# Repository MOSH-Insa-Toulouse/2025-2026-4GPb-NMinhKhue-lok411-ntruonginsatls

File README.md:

# Projet: Capteur Graphite à Crayon
MOSH projet crée par les étudiant.es en 4ème année de Génie Physique: 
**NGUYEN Minh Khue, VO Phuc Loc, TRUONG Nguyen Gia Khanh**

# Tableau de matière
- [Introduction](#introduction)
  - [Objectifs](#1-objectifs)
  - [Conception](#2-conception)
  - [Matériels nécessaires](#3-matériels-nécessaires)
  - [Livrables](#4-livrables)
- [Réalisation du projet](#réalisation-du-projet)
  - [Schémas](#1-schémas)
    - [Wiring diagram et Simulation LTspice](#11-wiring-diagram-et-simulation-ltspice)
    - [Connection diagram et KiCad](#12-connection-diagram-et-kicad)
  - [Software](#2-software)
    - [Code Arduino](#21-code-arduino)
    - [Application Android sur MIT App Inventor](#22-application-android-sur-mit-app-inventor)
  - [Banc de test](#3-banc-de-test)
    - [Principe](#31-principe)
    - [Résultats](#32-résultats)
- [Conclusion](#conclusion)
- [Contacts](#contacts)
## Introduction

### 1. Objectifs
Le projet est dans le cadre de l’UF « Du capteur au banc de test en open source hardware » en 4ᵉ année de Génie Physique à l’INSA Toulouse. Il est inspiré du rapport scientifique "Pencil Drawn Strain Gauges and Chemiresistors on Paper", publié en 2014 par Cheng-Wei Lin*, Zhibo Zhao*, Jaemyung Kim & Jiaxing Huang dans lequel les auteurs ont proposé un nouveau type de jauge de contrainte basé sur graphite. Le principe repose sur le fait que la résistance électrique du graphite varie lorsque le papier est déformé. En effet, la déformation modifie la distance entre les grains de graphite, ce qui entraîne une variation de la conductance du capteur. En mesurant cette variation de résistance, il est possible d’estimer la contrainte appliquée.

Le premier objectif est donc de concevoir un système qui nous permet de faire un banc de test en mesurant les capteurs simples à graphite pour les comparer avec les capteurs commerciales. De plus, le système doit être contrôlable. Le deuximème objectif est d'évaluer l'industriabilité de ce nouveau type de capteur à partir des mesures.

### 2. Conception
Pour regrouper plusieurs fonctions, cela vaut mieux que nous réalisons un shield Arduino. Nous pouvons contrôler les mesures soit manuellement avec un encoder rotatif via un écran OLED, soit à distance via un module Bluetooth et une application Android. Toutes ces idées sont synthétisé dans la figure ci-dessous.

Les détails sont décrits dans la partie de la réalisation.

(apres) nous avons manuellement soudé l'ensemble des modules arduino et composants électroniques (résistances, capacités, amplificateur opérationnel) au PCB imprimé.

(apres) Le Shield réalisé intègre un amplificateur de signal LTC1050 pour amplifier les faibles signaux des capteurs avec précision, un encodeur rotatif permettant de naviguer dans le menu et de modifier les valeurs de résistance via un potentiomètre, un écran OLED pour afficher clairement les menus et les informations, ainsi qu’un module Bluetooth assurant la communication sans fil avec un téléphone portable pour le contrôle et la supervision à distance du système.

### 3. Matériels nécessaires 
Avec la conception, nous avons décidé que ces composants listés ci-dessous sont suffisants, tout est disponible dans la salle d'instrumentation :
- 1 Carte Arduino UNO
- 1 Module Bluetooth (HC-05)
- 1 Encoder rotatif (Keyes KY-040)
- 1 Écran OLED
- 1 Capteur en graphite fait à l'aide de la couche d'un crayon de papier
- 1 Capteur de flexion commercial (LLC 1070)
- 1 Potentiomètre numérique (MCP41100)
- 1 Amplificateur de transimpédance (LTC1050)
- 2 Supports IC 
- 1 Résistance 1kΩ, 2 résistances 10kΩ, 2 résistances 100kΩ
- 3 condensateurs 100nF, 1 condensateur 1µF

### 4. Livrables
Plusieurs livrables sont contenus dans notre repositoire :
- **Un shield PCB connecté à une carte Arduino UNO** avec differents composants.
- Fiches techniques des composants (HC-05, Keyes KY-040, SSD 1306, LLC 1070, LTC1050, MCP41100)
- **Un code Arduino** qui gère les différents composants cités précédemments (mesures de résistance d'une jauge de contrainte faite en graphite, la communication avec un module Bluetooth, l'affichage sur l'écran OLED d'actions possibles et la gestion du potentiomètre digital permettant la calibration de notre capteur).
- **Une application Android** (grâce aux Tutoriels MIT App Inventor) permet de connecter le PCB et le code Arduino.
- La datasheet du capteur de contrainte en graphite.
- Les fichiers de simulation LTSpice et KiCad.

## Réalisation du projet

### 1. Schémas
La réalisation doit tout d'abord commencer par des schémas électriques tels que le Wiring diagram et le Connection diagram.

#### 1.1. Wiring diagram et Simulation LTspice
Ce diagramme a pour but de savoir comment on peut connecter le capteur à l'Arduino afin que les signaux des mesures soient captées par l'Arduino.

Nous souhaitons mesurer la résistance de notre capteur en graphite. Lorsque la résistance interne de notre capteur de graphite est de l'ordre du GΩ. Le courant généré lorsque nous appliquons une tension de 5V est très faible. Pour pouvoir utiliser ce signal, nous le faisons passer par un amplificateur transimpédance (ici nous choisissons LTC 1050) car il possède une capacité à accepter en entrée un courant très faible et un offset de tension bas. Ce montage est constitué d'un amplificateur opérationnel (AO) pour fournir un signal suffisamment large au convertisseur analogique-numérique (ADC) de l'Arduino UNO.

En plus de l'AOP, nous ajoutons 3 filtres:
- À l'entrée, un filtre passe bas passif composé de R1 et C1 de fréquence de coupure de 16Hz pour filtrer les bruits en courant sur le signal d'entrée.
- Une filtre passe bas actif composé de R3 et C4 de fréquence de coupure de 1.6Hz permettane de filtre la composante de bruit à 50Hz provenant du couplage avec le réseau éléctrique.
- En sortie, un dernier filtre composé de R6 et C2 de fréquence de 1.6kHz qui permet de retirer le bruit créé pendant le traitement i.e. bruits des alimentations, de l'horloge, etc.

La résistance R5 est placé en amont de l'AO pour le protéger contre des décharges électrostatiques. Pour notre simulation, nous avons placé la capacité C3 de sorte à ce qu'elle filtre le bruit de l'alimentation. Ainsi, la résistance R2 sera remplacé par une résistance variable (un potentiomètre digital) qui va nous permettre de régler le gain de notre AO en fonction de notre besoin.

Une fois dessiné le Wiring diagram, nous avons vérifié ses comportements et les valeurs de ses composants électriques (résistances, condensateurs,e tc.) grâce aux simulations du logiciel LTspice. (voir l'onglet caché ci-dessous)
<details>
<summary><strong>Simulation LTspice</strong></summary>

- **Fonctionnalité de condition nominale**

Le courant d’entrée Isens varie entre 50 nA et 100 nA, ce qui entraîne une variation de la tension Vep appliquée à l’entrée non-inverseur V+ du LTC1050, entre 5 mV et 10 mV.

Le gain de l’amplificateur du LTC1050 est défini par : G = 1 + R3/R2 = 101. Par conséquent, la valeur de la tension de sortie du LTC1050 varie entre 0.5 V et 1 V.

Au départ, le signal exprimé en décibels est de 140 dB, ce qui correspond à : 20 log(VADC / Isens).

Le microcontrôleur utilisé est un Arduino UNO, basé sur un microcontrôleur AVR avec une fréquence d’échantillonnage maximale fech = 200 kHz.
Comme la conversion analogique-numérique se fait sur 13 bits, la fréquence d’échantillonnage réelle est limitée à 15.4 kHz.

D'après le théorème de Nyquist, la fréquence maximale du signal que l'on peut correctement numériser doit donc être inférieure à la moitié de cette valeur :
fsignal < fech/2 = 7.7 kHz.

- **Modélisation du capteur**
  - Le bruit à 50 Hz, généré notamment par l'écran TFT (bruit de type secteur), est clairement observé dans le spectre du signal. Pour l’atténuer, on agit sur le condensateur C4 du filtre passe-bas.

  - Lorsque la valeur de C4 est augmentée à 10 µF, le pic de bruit à 50 Hz est fortement réduit, ce qui indique une amélioration de l’atténuation dans les basses fréquences.

  - En revanche, si on diminue la valeur de C4, le bruit augmente, montrant que la fréquence de coupure du filtre remonte et que le bruit secteur passe plus facilement.

- **Résultat**
Une photo démontrant que notre circuit permet une amplification efficace du signal délivré par le capteur :

</details>

#### 1.2. Connection diagram et KiCad
Après le Wiring diagram, nous avons dessiné le diagramme des connexions afin de déterminer les connexions entre les broches des différents composants. Nous l'avons réalisé avec le logiciel KiCad car ce logiciel nous aiderait les étapes après.

Nous vous expliquons les réalisations sur KiCad :

- Réalisation des symboles et des empreints :
Pour commencer notre PCB (Printed Circuit Board), il est nécessaire de créer les symboles et les empreintes des composants qui ne sont pas disponibles dans la bibliothèque de KiCad. Nous avons réalisé les symboles du module Bluetooth, de l'encodeur rotatif, de l'écran OLED, du capteur de flexion et du capteur en graphite, afin de les ajouter au schéma de connexion. Ensuite, ces symboles ont été associés à une empreinte trouvée sur des sites de libre téléchargement.

- Réalisation du schéma électronique (Connection diagram) :
Ensuite, le schéma électronique est à construire. Dans cette partie, les différentes connexions entre composants sont définies et les pins de la carte Arduino sont attribués à chacun des composants.

- Réalisation du routage :
L'objectif ici était d'allouer un branchement sur les entrées d'une carte Arduino UNO à chaque module. Nous avons aussi pour but de faire le moins possible de via (pont traversant permettant de chavaucher un routage). Le circuit imprimé a été dessiné avec une attention particulière portée à la disposition des pistes pour minimiser les couplages parasites et faciliter le routage manuel.

L'ensemble des fichiers KiCad est disponible dans le dossier [Shield TP Arduino par KiCad](Shield%20TP%20Arduino%20par%20KiCad).

#### 1.3. Résultat
L'image de 3D du PCB :

Le PCB physique :

### 2. Software

Nous avons passé à la partie de software une fois celle de hardware est finie.

#### 2.1. Code Arduino
Le code Arduino permet de lire les valeurs du capteur en graphite, de gérer l'affichage d'un Menu sur l'écran OLED, la communication par Bluetooth avec l'application Android et le contrôle via l'encodeur rotatif.

Le code Arduino est disponible dans le dossier [Programme Arduino](Programme%20Arduino).

#### 2.2. Application Android sur MIT App Inventor
Cette application permet de communiquer avec le système de mesure via Bluetooth et d’afficher les valeurs de résistance des capteurs.

Lorsque la connexion Bluetooth est réussie, le bouton Connected devient vert, ce qui indique que la liaison est établie.

L’application propose deux modes de mesure :
- Measure Graphite : mesure la résistance du capteur graphite ;
- Measure Flex Sensor : mesure la résistance du capteur flex en fonction du temps.
Les valeurs mesurées sont affichées sur le graphique au centre de l’écran. À la fin de la mesure, les données sont regroupées, la valeur moyenne de la résistance est calculée, puis affichée en bas de l’interface.

### 3. Banc de test
Pour valider le fonctionnement du système, nous faisons évaluer les performances de notre capteur à travers un banc de test.

#### 3.1. Principe

Un modèle 3D composé de fentes circulaires de différents rayons est utilisé pour le banc de test. En insérant le capteur dans ces fentes, une déformation est induite en fonction de son orientation (traction ou compression). La déformation est inversement proportionnelle au rayon des fentes circulaires, selon la relation suivante : 
ε = e / 2R

Où :
ε : déformation
e : allongement imposé
R : rayon de la fente (0,2 mm)

Ce système permet de contrôler précisément la déformation du capteur en choisissant simplement un rayon de fente spécifique.

<details>
<summary><strong>Explication de la physique derrière la capteur à graphite</strong></summary>
Lorsque le capteur est déformé, sa résistance varie naturellement. Ce phénomène s’explique principalement par les changements de distance entre les atomes de carbone qui le composent.

En traction, les atomes s’éloignent les uns des autres. Les chemins conducteurs entre les deux extrémités du capteur deviennent alors moins nombreux et moins continus. Les électrons circulent donc plus difficilement, ce qui entraîne une augmentation de la résistance.

À l’inverse, en compression, les atomes se rapprochent. Les contacts entre particules sont facilités, ce qui crée davantage de chemins conducteurs. Les électrons passent alors plus facilement et la résistance diminue.

On observe également que la résistance diminue lorsque la dureté du crayon augmente. Cela s’explique simplement par une plus faible proportion de carbone dans le matériau.

</details>
  
#### 3.2. Résultats

Par la suite, nous avons caractérisé notre capteur en graphite afin de reproduire les résultats présentés dans l’étude mentionnée ci-dessus. La tension aux bornes du capteur est mesurée puis convertie en valeur de résistance. Cette résistance est ensuite tracée en fonction de la déformation appliquée.

Les graphiques ci-dessus montrent la variation relative de la résistance du capteur en fonction de la déformation dans deux modes : traction et compression. Des droites de régression linéaire passant par l’origine ont été ajustées, montrant que la variation relative de résistance (ΔR/R₀) évolue linéairement avec la déformation.

Variation des résistances en fonction de déformation en mode traction

Variation des résistances en fonction de déformation en mode compression

**Remarque**
Le capteur à graphite n’est pas très exacte, car les valeurs de résistance changent beaucoup d’une mesure à l’autre, même quand on répète la même manipulation. Cela signifie que les résultats ne sont pas stables et qu’il est difficile de faire confiance aux mesures obtenues. Cette instabilité peut venir de plusieurs facteurs. Par exemple, le papier support peut se plier ou s’abîmer légèrement; le dépôt de graphite peut se fissurer ou se déplacer; le capteur absorbe l'humidité de son environnement. À l’intérieur du capteur, le courant passe grâce au contact entre de petites particules de graphite. Si ces contacts changent après chaque déformation, même un peu, la résistance peut varier fortement.

En comparaison, un capteur industriel comme un flex sensor est conçu pour être plus robuste. Sa structure interne est mieux contrôlée, ce qui permet d’obtenir des mesures plus stables et répétables. Les résultats changent donc beaucoup moins entre plusieurs essais, ce qui le rend plus fiable dans des applications pratiques. Cependant, si on ne concernait que les applicaitons qui ne requièrent pas des mesures exactes mais que une déformation, ce type de capteur à graphite est ainsi un bon outil. 

## Conclusion

Dans ce travail, nous avons fabriqué un capteur de déformation en graphite sur les papiers et avons étudié comment sa résistance change lors des déformations.

Les résultats montrent que la résistance varie bien avec la déformation, ce qui confirme le principe du capteur. Cependant, les valeurs mesurées ne sont pas stables et changent d’une mesure à l’autre. Cela est probablement dû à la structure du graphite, qui n’est pas uniforme, ainsi qu’à la qualité des contacts et au support en papier qui peut se déformer.

Ainsi, même si ce capteur est simple et peu coûteux, il reste peu exacte dans sa forme actuelle. Il serait donc difficile de l’utiliser en industrie pour les applications requises l'exactitude. Par contre, pour les applications de détection de déformation, il est bien adapté.

## Contacts
Pour toutes les informations complémentaires: 
### Étudiant.es réalisé.es :
- NGUYEN Minh Khue : mngu@insa-toulouse.fr
- VO Phuc Loc : pvo@insa-toulouse.fr
- TRUONG Nguyen Gia Khanh : ntruong@insa-toulouse.fr

### Enseignant.es :
- Jérémie Grisolia : jeremie.grisolia@insa-toulouse.fr
- Arnauld Biganzoli : arnauld.biganzoli@insa-toulouse.fr
- Cathy Crouzet : crouzet@insa-toulouse.fr
- Benjamin Mestre : benjamin.mestre@scalian.com

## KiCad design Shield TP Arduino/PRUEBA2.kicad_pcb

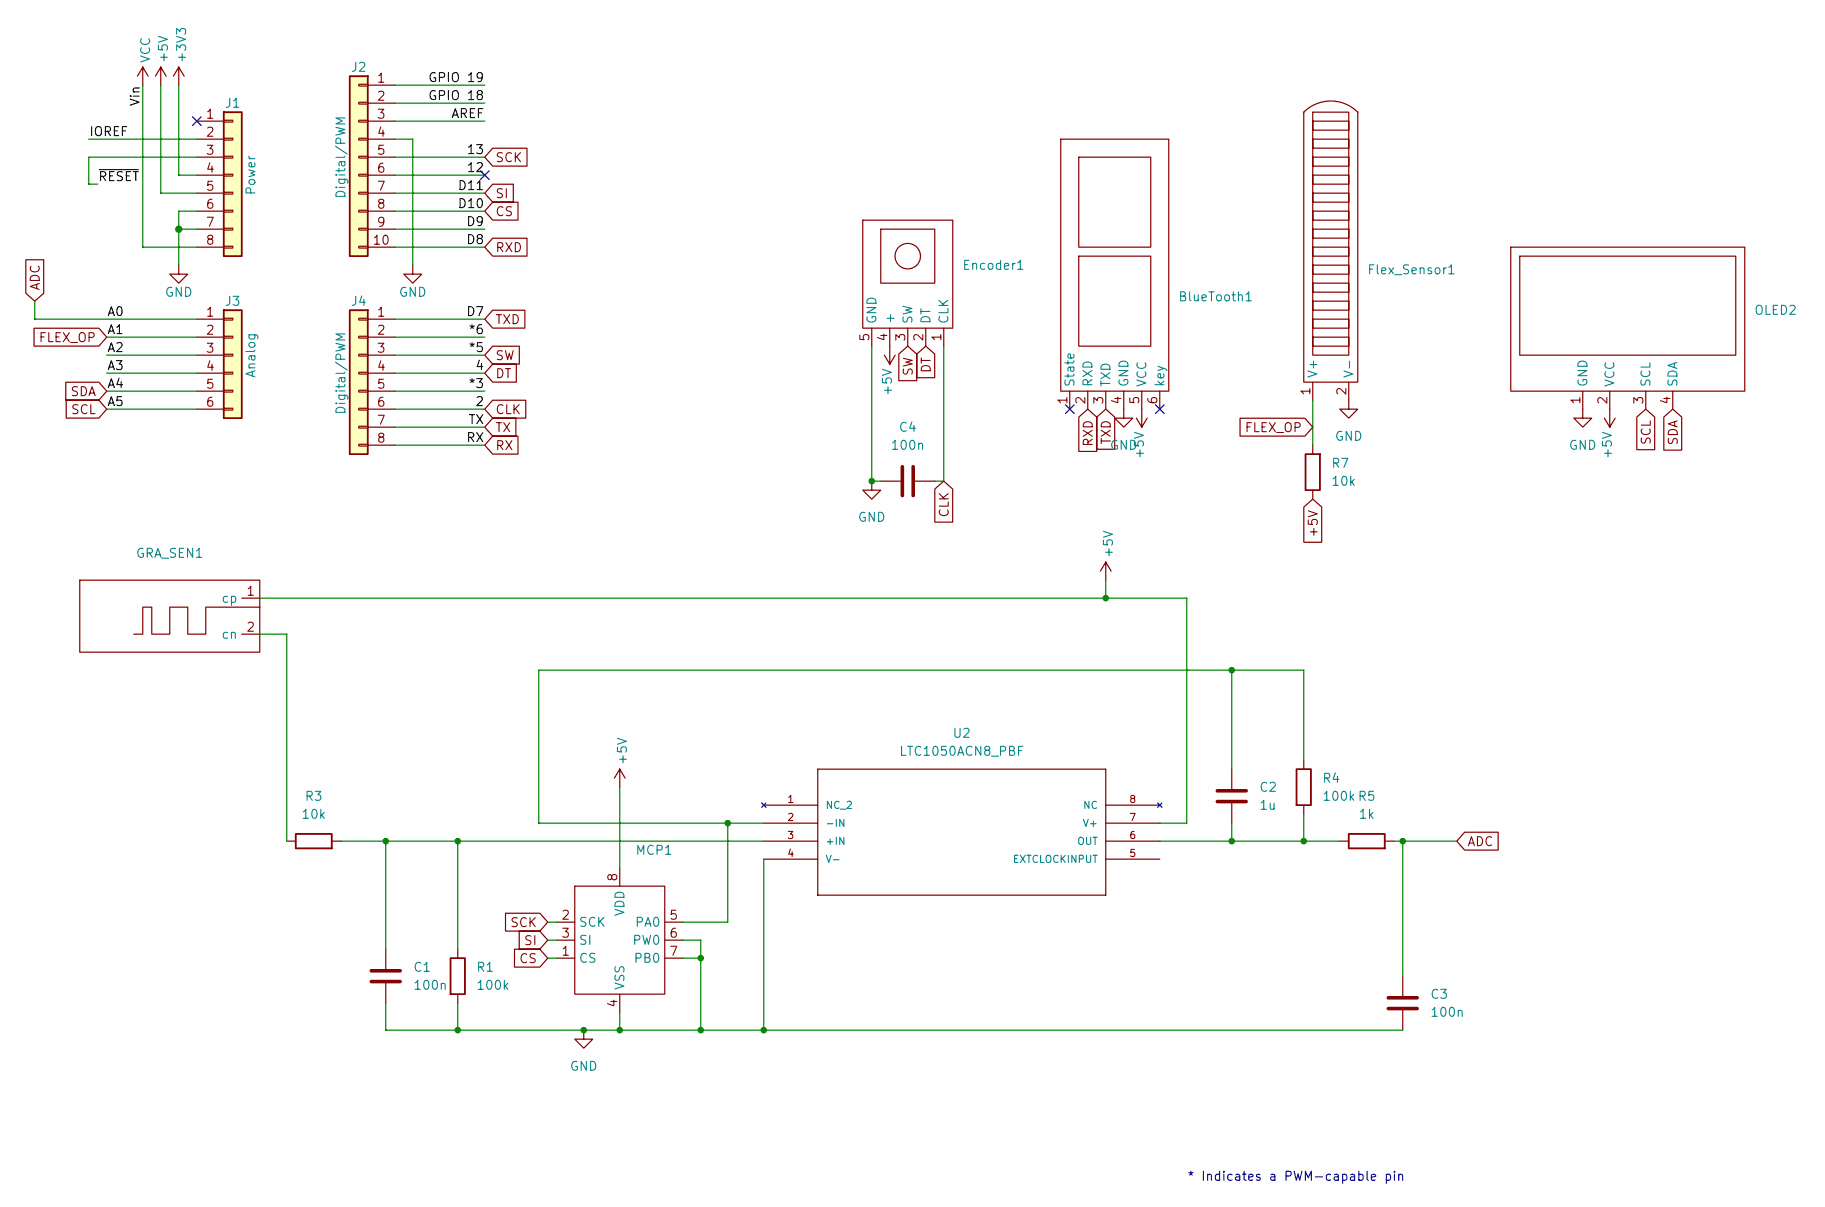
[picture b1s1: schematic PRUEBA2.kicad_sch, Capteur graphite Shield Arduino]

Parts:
BlueTooth1: Bluetooth
C1, C3, C4: 100n; C_Disc_D4.7mm_W2.5mm_P5.00mm
C2: 1u; C_Rect_L7.0mm_W2.5mm_P5.00mm
Encoder1: Encoder_rotation
Flex_Sensor1: Sensor
GRA_SEN1: Sensor
J1: Power; PinSocket_1x08_P2.54mm_Vertical
J2: Digital/PWM; PinSocket_1x10_P2.54mm_Vertical
J3: Analog; PinSocket_1x06_P2.54mm_Vertical
J4: Digital/PWM; PinSocket_1x08_P2.54mm_Vertical
MCP1: DIP-8_296_ELL
OLED2: OLED
R1, R4: 100k; R_Axial_DIN0207_L6.3mm_D2.5mm_P15.24mm_Horizontal
R3, R7: 10k; R_Axial_DIN0207_L6.3mm_D2.5mm_P15.24mm_Horizontal
R5: 1k; R_Axial_DIN0207_L6.3mm_D2.5mm_P15.24mm_Horizontal
U2: LTC1050ACN8_PBF; DIP-8_296_ELL

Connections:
+3V3: J1.4
+5V: BlueTooth1.5 (VCC), Encoder1.4 (+), GRA_SEN1.1 (cp), J1.5, MCP1.8 (VDD), OLED2.2 (VCC), R7.1, U2.7 (V+)
/12: J2.6
/*3: J4.5
/*6: J4.2
/A2: J3.3
/A3: J3.4
/AREF: J2.3
/D9: J2.9
/GPIO 18: J2.2
/GPIO 19: J2.1
/IOREF: J1.2
/~RESET: J1.3
ADC: C3.1, J3.1, R5.2
CLK: C4.1, Encoder1.1 (CLK), J4.6
CS: J2.8, MCP1.1 (CS)
DT: Encoder1.2 (DT), J4.4
FLEX_OP: Flex_Sensor1.1 (V+), J3.2, R7.2
GND: BlueTooth1.4 (GND), C1.2, C3.2, C4.2, Encoder1.5 (GND), Flex_Sensor1.2 (V-), J1.6, J1.7, J2.4, MCP1.4 (VSS), MCP1.6 (PW0), MCP1.7 (PB0), OLED2.1 (GND), R1.2, U2.4 (V-)
unnamed: GRA_SEN1.2 (cn), R3.1
unnamed: C2.1, MCP1.5 (PA0), R4.1, U2.2 (-IN)
unnamed: C1.1, R1.1, R3.2, U2.3 (+IN)
unnamed: C2.2, R4.2, R5.1, U2.6 (OUT)
RX: J4.8
RXD: BlueTooth1.2 (RXD), J2.10
SCK: J2.5, MCP1.2 (SCK)
SCL: J3.6, OLED2.3 (SCL)
SDA: J3.5, OLED2.4 (SDA)
SI: J2.7, MCP1.3 (SI)
SW: Encoder1.3 (SW), J4.3
TX: J4.7
TXD: BlueTooth1.3 (TXD), J4.1
VCC: J1.8

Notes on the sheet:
* Indicates a PWM-capable pin

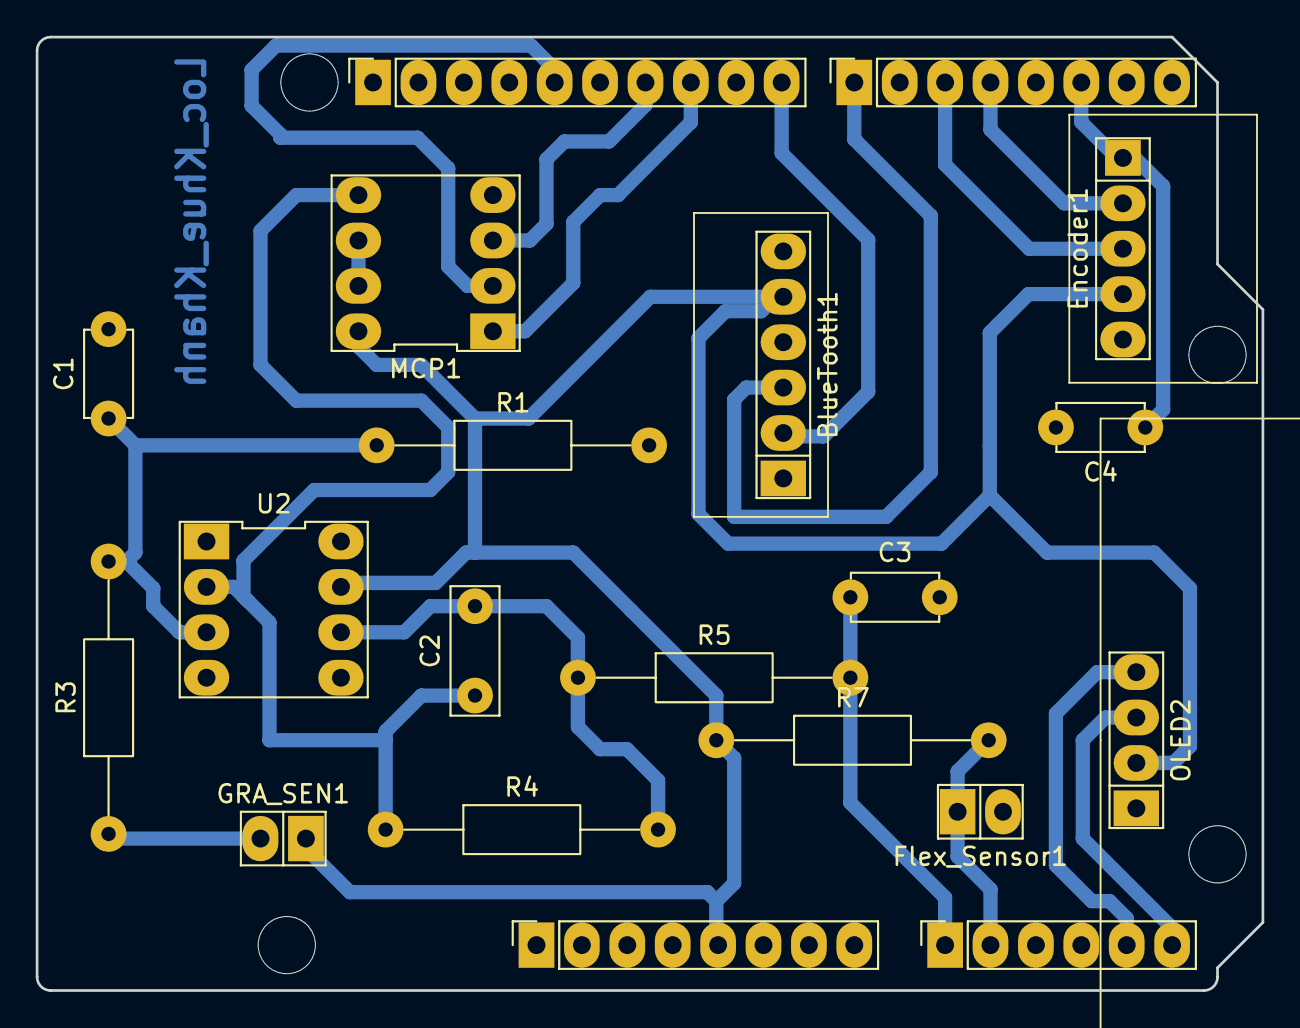
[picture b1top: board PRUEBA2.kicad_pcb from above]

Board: 2 copper layers, 68.6 x 53.3 mm, 24 parts (0 on the bottom side), 18 nets.

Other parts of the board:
MH1, MH2, MH3, MH4: MountingHole_3.2mm

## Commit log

2026-02-10 Create XQnh file
    XAnh djnh cap
2026-02-10 Xanh djinh
2026-02-21 module 3D and pcb
2026-02-24 Update README with more detailed sections
2026-02-24 Finish PCB files
2026-02-25 new update PCB
2026-03-06 programme arduino
2026-03-06 Menu oled, miss bluetooth control
2026-03-06 update measure flex/graphtie sensor
2026-03-22 Variation des meseures de capteurs
2026-03-22 Variation des mesures de capteurs
2026-03-25 Update README
    Added a section for project conception and listed required materials.
2026-04-08 Images
2026-04-08 update images
2026-04-08 Add LTSpice files
2026-04-08 Add LTSpice (for real)
2026-04-08 Update README
    Test Toggle list in Markdown
2026-04-09 new updates for ltspice
2026-04-10 Remove empty details tag in README
    Removed unnecessary details tag from the README.
2026-04-12 Add MIT app files
2026-04-12 datasheet
2026-04-12 test bench
2026-04-12 datasheet update
2026-04-12 Updates image
2026-04-13 modifier donnees
2026-04-14 updates images
2026-04-15 MIT and Code Arduino
2026-04-16 updates banc de test
2026-04-16 banc de test
2026-04-17 Add files via upload
    file apk
2026-04-29 New udpdate banc de test
2026-05-30 Edit texts
2026-05-30 Conception image
2026-05-30 Rename image.png to conception_image.png
2026-05-30 Edit the beginning
2026-05-30 Make objectives clearer
2026-05-30 système image
2026-05-30 Rename image.png to system_image.png
2026-05-30 Replace shield assembly image with system image
    Updated images in README and added new system image.
2026-05-30 Reorganise sections
2026-05-30 Edit until Connection diagram and KiCad
    Need to continue writing the section about KiCad
2026-05-31 Revise section headings and content structure
    Updated section headings and improved organization in the README.
2026-05-31 Updating README
2026-05-31 Finito edit README
    hopefully
2026-05-31 change files
2026-05-31 Changes again
2026-05-31 change file names
2026-05-31 Fix typographical errors in README
2026-05-31 Revise README
2026-05-31 Fix links in README for KiCad and Arduino code
